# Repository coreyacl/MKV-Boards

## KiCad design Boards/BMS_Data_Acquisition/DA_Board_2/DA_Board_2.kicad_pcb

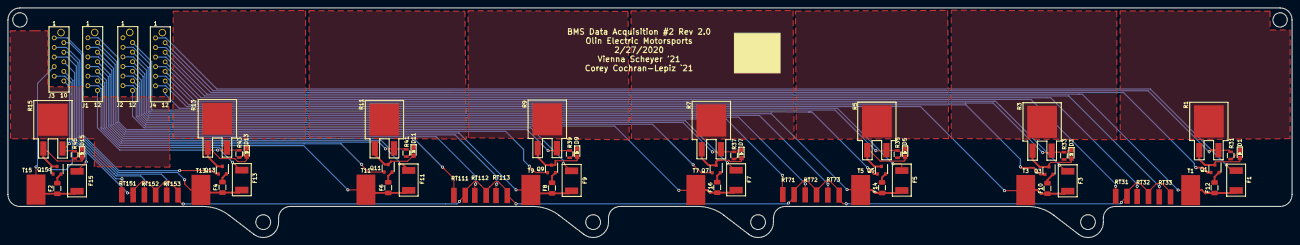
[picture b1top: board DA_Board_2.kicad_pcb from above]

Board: 2 copper layers, 340.1 x 60.8 mm, 72 parts (0 on the bottom side), 69 nets.

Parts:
D1, D3, D5, D7, D9, D11, D13, D15: LED_0805; LED_0805_OEM
F1, F3, F5, F7, F9, F11, F13, F15: 200mA_Fuse; Fuse_1812
F2, F4, F6, F8, F10, F12, F14, F16: 1.5A_Fuse; Fuse_1206
J1, J2, J4: MM_M_VT_12; micromatch_female_vert_12
J3: MM_M_VT_10; micromatch_female_vert_10
Q1, Q3, Q5, Q7, Q9, Q11, Q13, Q15: BSS308PE; SOT-23-3_OEM
R1, R3, R5, R7, R9, R11, R13, R15: R_3.3_25W_TO163; PWR163
R31, R33, R35, R37, R39, R41, R43, R45: R_475; R_0805_OEM
RT31, RT32, RT33, RT71, RT72, RT73, RT111, RT112, RT113, RT151, RT152, RT153: Thermistor
T1, T3, T5, T7, T9, T11, T13, T15: Tab_Connect_BMS; Tab_connect_BMS

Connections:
/C1: F1.2, J4.1
/C3: F3.2, J4.8
/C3_T1: J4.7, RT31.1
/C3_T2: J4.6, RT32.1
/C3_T3: J4.5, RT33.1
/C5: F5.2, J4.12
/C7: F7.2, J2.8
/C7_T1: J2.7, RT71.1
/C7_T2: J2.6, RT72.1
/C7_T3: J2.5, RT73.1
/C9: F9.2, J2.12
/C11: F11.2, J1.7
/C11_T1: J1.6, RT111.1
/C11_T2: J1.5, RT112.1
/C11_T3: J1.4, RT113.1
/C13: F13.2, J1.11
/C15: F15.2, J3.8
/C15_T1: J3.5, RT151.1
/C15_T2: J3.4, RT152.1
/C15_T3: J3.3, RT153.1
/GND1: J3.6, RT31.2, RT32.2, RT33.2, RT71.2, RT72.2, RT73.2, RT111.2, RT112.2, RT113.2, RT151.2, RT152.2, RT153.2
/PWR1: J4.2, R1.2, R31.2
/PWR2: F1.1, F12.1, J4.4, T1.1
/PWR3: J4.9, R3.2, R33.2
/PWR4: F3.1, F10.1, J4.11, T3.1
/PWR5: J2.2, R5.2, R35.2
/PWR6: F5.1, F14.1, J2.4, T5.1
/PWR7: J2.9, R7.2, R37.2
/PWR8: F7.1, F16.1, J2.11, T7.1
/PWR9: J1.1, R9.2, R39.2
/PWR10: F8.1, F9.1, J1.3, T9.1
/PWR11: J1.8, R11.2, R41.2
/PWR12: F6.1, F11.1, J1.10, T11.1
/PWR13: J1.12, R13.2, R43.2
/PWR14: F4.1, F13.1, J3.2, T13.1
/PWR15: J3.10, R15.2, R45.2
/PWR16: F2.1, F15.1, J3.7, T15.1
/Q1: J4.3, Q1.1
/Q3: J4.10, Q3.1
/Q5: J2.3, Q5.1
/Q7: J2.10, Q7.1
/Q9: J1.2, Q9.1
/Q11: J1.9, Q11.1
/Q13: J3.1, Q13.1
/Q15: J3.9, Q15.1
unnamed: D1.1, R31.1
unnamed: D1.2, Q1.3, R1.1
unnamed: D3.1, R33.1
unnamed: D3.2, Q3.3, R3.1
unnamed: D5.1, R35.1
unnamed: D5.2, Q5.3, R5.1
unnamed: D7.1, R37.1
unnamed: D7.2, Q7.3, R7.1
unnamed: D9.1, R39.1
unnamed: D9.2, Q9.3, R9.1
unnamed: D11.1, R41.1
unnamed: D11.2, Q11.3, R11.1
unnamed: D13.1, R43.1
unnamed: D13.2, Q13.3, R13.1
unnamed: D15.1, R45.1
unnamed: D15.2, Q15.3, R15.1
unnamed: F2.2, Q15.2
unnamed: F4.2, Q13.2
unnamed: F6.2, Q11.2
unnamed: F8.2, Q9.2
unnamed: F10.2, Q3.2
unnamed: F12.2, Q1.2
unnamed: F14.2, Q5.2
unnamed: F16.2, Q7.2

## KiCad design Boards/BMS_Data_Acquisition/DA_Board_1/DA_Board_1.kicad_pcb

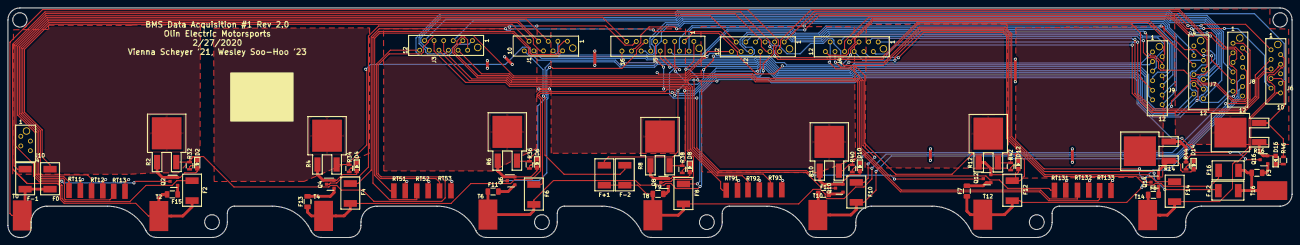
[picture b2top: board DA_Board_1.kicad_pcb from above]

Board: 2 copper layers, 340.1 x 60.8 mm, 85 parts (1 on the bottom side), 103 nets.

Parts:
D2, D4, D6, D8, D10, D12, D14, D16: LED_0805; LED_0805_OEM
F0, F2, F4, F6, F8, F10, F12, F14, F16: 200mA_Fuse; Fuse_1812
F1, F3, F5, F7, F9, F11, F13, F15: 1.5A_Fuse; Fuse_1206
F+1, F+2: 200mA_Fuse; Fuse_1812
F-1, F-2: 200mA_Fuse; Fuse_1812
J1, J6: MM_M_VT_10; micromatch_female_vert_10
J2, J3, J4, J7, J8#2, J9: MM_M_VT_12; micromatch_female_vert_12
J5: MM_M_VT_16; micromatch_female_vert_16
J8, J10: MM_F_VT_04; micromatch_female_vert_4
Q2, Q4, Q6, Q8, Q10, Q12, Q14, Q16: BSS308PE; SOT-23-3_OEM
R2, R4, R6, R8, R10, R12, R14, R16: R_3.3_25W_TO163; PWR163
R32, R34, R36, R38, R40, R42, R44, R46: R_475; R_0805_OEM
RT11, RT12, RT13, RT51, RT52, RT53, RT91, RT92, RT93, RT131, RT132, RT133: Thermistor
T0, T2, T4, T6, T8, T10, T12, T14, T16: Tab_Connect_BMS; Tab_connect_BMS

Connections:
/C0: F0.2, J1.9
/C1: J1.8, J9.1
/C1_T1: J1.7, RT11.1
/C1_T2: J1.6, RT12.1
/C1_T3: J1.5, RT13.1
/C2: F2.2, J2.11
/C3: J1.4, J9.8
/C3_T1: J2.9, J9.7
/C3_T2: J2.8, J9.6
/C3_T3: J2.7, J9.5
/C4: F4.2, J2.10
/C5: J1.3, J9.12
/C5_T1: J1.2, RT51.1
/C5_T2: J1.1, RT52.1
/C5_T3: J3.12, RT53.1
/C6: F6.2, J2.6
/C7: J3.11, J7.8
/C7_T1: J2.2, J7.7
/C7_T2: J2.1, J7.6
/C7_T3: J4.12, J7.5
/C8: F8.2, J2.3
/C9: J3.10, J7.12
/C9_T1: J3.9, RT91.1
/C9_T2: J3.8, RT92.1
/C9_T3: J3.7, RT93.1
/C10: F10.2, J4.11
/C11: J3.6, J8#2.7
/C11_T1: J4.9, J8#2.6
/C11_T2: J4.8, J8#2.5
/C11_T3: J4.7, J8#2.4
/C12: F12.2, J4.10
/C13: J3.5, J8#2.11
/C13_T1: J3.4, RT131.1
/C13_T2: J3.3, RT132.1
/C13_T3: J3.2, RT133.1
/C14: F14.2, J4.6
/C15: J3.1, J6.8
/C15_T1: J4.3, J6.5
/C15_T2: J4.2, J6.4
/C15_T3: J4.1, J6.3
/C16: F16.2, J4.4
/GND1: J2.12, J6.6, RT11.2, RT12.2, RT13.2, RT51.2, RT52.2, RT53.2, RT91.2, RT92.2, RT93.2, RT131.2, RT132.2, RT133.2
/PWR1: F0.1, F-1.1, J9.2, T0.1
/PWR2: J9.4, R2.2, R32.2
/PWR3: F2.1, F15.1, J9.9, T2.1
/PWR4: J9.11, R4.2, R34.2
/PWR5: F4.1, F13.1, J7.2, T4.1
/PWR6: J7.4, R6.2, R36.2
/PWR7: F6.1, F11.1, J7.9, T6.1
/PWR8: J7.11, R8.2, R38.2
/PWR9: F8.1, F9.1, F+1.1, F-2.1, J8#2.1, T8.1
/PWR10: J8#2.3, R10.2, R40.2
/PWR11: F1.1, F10.1, J8#2.8, T10.1
/PWR12: J8#2.10, R12.2, R42.2
/PWR13: F7.1, F12.1, J8#2.12, T12.1
/PWR14: J6.2, R14.2, R44.2
/PWR15: F5.1, F14.1, J6.10, T14.1
/PWR16: J6.7, R16.2, R46.2
/Q1: J5.16, J9.3
/Q2: J5.15, Q2.1
/Q3: J5.14, J9.10
/Q4: J5.13, Q4.1
/Q5: J5.12, J7.3
/Q6: J5.11, Q6.1
/Q7: J5.10, J7.10
/Q8: J5.9, Q8.1
/Q9: J5.8, J8#2.2
/Q10: J5.7, Q10.1
/Q11: J5.6, J8#2.9
/Q12: J5.5, Q12.1
/Q13: J5.4, J6.1
/Q14: J5.3, Q14.1
/Q15: J5.2, J6.9
/Q16: J5.1, Q16.1
/V+1: F+1.2, J4.5
/V+2: F+2.2, J2.5
/V-1: F-1.2, J2.4
/V-2: F-2.2, J1.10
unnamed: D2.1, R32.1
unnamed: D2.2, Q2.3, R2.1
unnamed: D4.1, R34.1
unnamed: D4.2, Q4.3, R4.1
unnamed: D6.1, R36.1
unnamed: D6.2, Q6.3, R6.1
unnamed: D8.1, R38.1
unnamed: D8.2, Q8.3, R8.1
unnamed: D10.1, R40.1
unnamed: D10.2, Q10.3, R10.1
unnamed: D12.1, R42.1
unnamed: D12.2, Q12.3, R12.1
unnamed: D14.1, R44.1
unnamed: D14.2, Q14.3, R14.1
unnamed: D16.1, R46.1
unnamed: D16.2, Q16.3, R16.1
unnamed: F1.2, Q10.2
unnamed: F3.2, Q16.2
unnamed: F5.2, Q14.2
unnamed: F7.2, Q12.2
unnamed: F9.2, Q8.2
unnamed: F11.2, Q6.2
unnamed: F13.2, Q4.2
unnamed: F15.2, Q2.2
unnamed: F3.1, F16.1, F+2.1, T16.1

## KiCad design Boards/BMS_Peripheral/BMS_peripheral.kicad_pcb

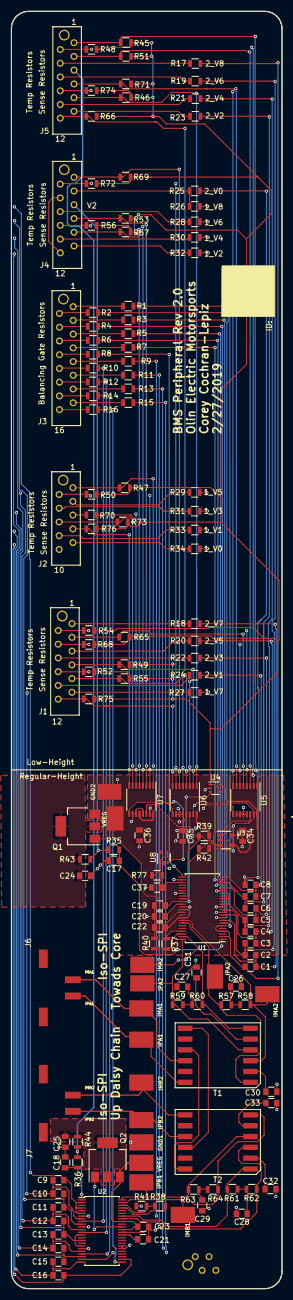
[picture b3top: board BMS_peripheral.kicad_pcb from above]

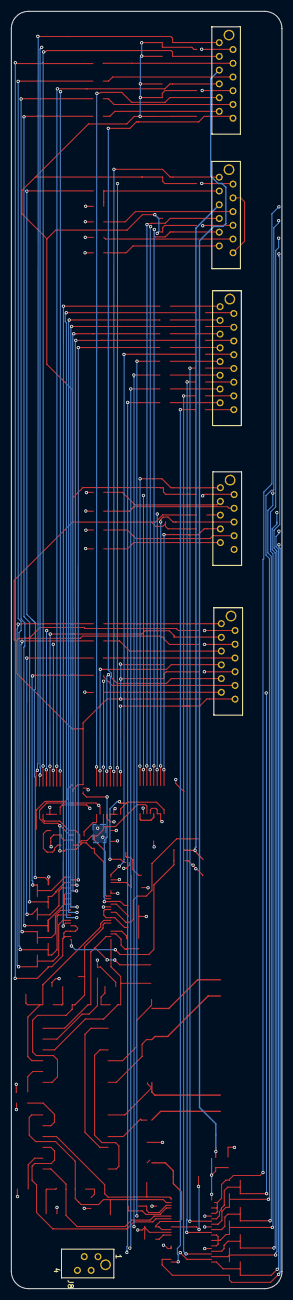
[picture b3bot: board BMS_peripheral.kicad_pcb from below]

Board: 4 copper layers, 50.0 x 236.2 mm, 148 parts (6 on the bottom side), 138 nets.

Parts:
C1, C2, C3, C4, C5, C6, C7, C8, C9, C10, C11, C12, C13, C14, C15, C16, C26, C27, C28, C29, C30, C31, C32, C33, C37: C_10nF; C_0805_OEM
C17, C18, C24, C25: C_0.1uF; C_0805_OEM
C19, C20, C21, C22, C23: 1uF; C_0805_OEM
C34, C35, C36: C_1uF; C_0805_OEM
J1, J4: MM_F_VT_12; micromatch_female_vt_12
J2: MM_F_VT_10; micromatch_female_vert_10
J3: MM_F_VT_16; micromatch_female_vert_16
J5: MM_M_VT_12; micromatch_female_vt_12
J6, J7: MicroFit_RA_V_2_SMD; MicroFit_RA_2_SMD
J8: MM_F_VT_04; micromatch_female_vert_4
Q1, Q2: NSS1C201MZ4; SOT-223
R1, R2, R3, R4, R5, R6, R7, R8, R9, R10, R11, R12, R13, R14, R15, R16, R39, R42: R_4.99K; R_0805_OEM
R17, R18, R19, R20, R21, R22, R23, R24, R25, R26, R27, R28, R29, R30, R31, R32, R33, R34, R35, R36, R43, R44, R77: R_100; R_0805_OEM
R37, R38, R40, R41: R_1K; R_0805_OEM
R45, R46, R47, R48, R49, R50, R51, R52, R53, R54, R55, R56, R65, R66, R67, R68, R69, R70, R71, R72, R73, R74, R75, R76: R_100K; R_0805_OEM
R57, R58, R59, R60, R61, R62, R63, R64: R_60.4; R_0805_OEM
T1, T2: T_LAN_SM91501ALE
TP1, TP2, TP3, TP4, TP5, TP6, TP7, TP8, TP9, TP10, TP11, TP12, TP13, TP14: Test_Point_SMD
U1, U2: LTC6811-1; TSSOP-48_LTC6811-1
U3: 24AA01; SOT-23-5_OEM_24AA01
U4, U8: MCP6001T-I-LT; SOT-353_SC-70-5
U5, U6, U7: LTC1380IGN; SSOP-16_3.9x4.9mm_P0.635mm

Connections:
/C0: J2.9, R34.1
/C1: J2.8, R33.1
/C1_T1: J2.7, R76.2, U7.8
/C1_T2: J2.6, R73.2, U7.7
/C1_T3: J2.5, R70.2, U7.6
/C2: J4.11, R32.1
/C3: J2.4, R31.1
/C3_T1: J4.9, R67.2, U7.5
/C3_T2: J4.8, R56.2, U7.4
/C3_T3: J4.7, R53.2, U7.3
/C4: J4.10, R30.1
/C5: J2.3, R29.1
/C5_T1: J2.2, R50.2, U7.2
/C5_T2: J2.1, R47.2, U7.1
/C5_T3: J1.12, R75.2, U6.8
/C6: J4.6, R28.1
/C7: J1.11, R27.1
/C7_T1: J4.2, R72.2, U6.7
/C7_T2: J4.1, R69.2, U6.6
/C7_T3: J5.12, R66.2, U6.5
/C8: J4.3, R25.1, R26.1
/C9: J1.10, R24.1
/C9_T1: J1.9, R55.2, U6.4
/C9_T2: J1.8, R52.2, U6.3
/C9_T3: J1.7, R49.2, U6.2
/C10: J5.11, R23.1
/C11: J1.6, R22.1
/C11_T1: J5.9, R46.2, U6.1
/C11_T2: J5.8, R74.2, U5.8
/C11_T3: J5.7, R71.2, U5.7
/C12: J5.10, R21.1
/C13: J1.5, R20.1
/C13_T1: J1.4, R68.2, U5.6
/C13_T2: J1.3, R65.2, U5.5
/C13_T3: J1.2, R54.2, U5.4
/C14: J5.6, R19.1
/C15: J1.1, R18.1
/C15_T1: J5.3, R51.2, U5.3
/C15_T2: J5.2, R48.2, U5.2
/C15_T3: J5.1, R45.2, U5.1
/C16: J5.4, R17.1
/GND1: C18.2, C21.2, C23.2, C25.2, C28.2, C29.2, C32.2, C33.2, J4.4, J4.12, R41.2, TP1.1, U2.30, U2.31, U2.36
/GND2: C17.2, C19.2, C20.2, C22.2, C24.2, C26.2, C27.2, C30.2, C31.2, C34.2, C35.2, C36.2, C37.2, J2.10, R40.2, TP2.1, U1.30, U1.31, U1.36, U3.2, U3.5, U4.2, U5.10, U5.11, U5.12, U5.13, U6.10, U6.11, U6.12, U7.10, U7.11, U7.13, U8.2
/IMA1: R62.2, T2.3, U2.41
/IMA2: R58.2, T1.3, TP5.1, U1.41
/IMB1: R64.2, T2.6, TP7.1, U2.47
/IMB2: R60.2, T1.6, TP10.1, U1.47
/IPA1: R61.1, T2.1, U2.42
/IPA2: R57.1, T1.1, TP8.1, U1.42
/IPB1: R63.1, T2.4, TP6.1, U2.48
/IPB2: R59.1, T1.4, TP9.1, U1.48
/Q1: J3.16, R16.2
/Q2: J3.15, R15.2
/Q3: J3.14, R14.2
/Q4: J3.13, R13.2
/Q5: J3.12, R12.2
/Q6: J3.11, R11.2
/Q7: J3.10, R10.2
/Q8: J3.9, R9.2
/Q9: J3.8, R8.2
/Q10: J3.7, R7.2
/Q11: J3.6, R6.2
/Q12: J3.5, R5.2
/Q13: J3.4, R4.2
/Q14: J3.3, R3.2
/Q15: J3.2, R2.2
/Q16: J3.1, R1.2
/SCL: R42.2, U1.33, U3.1, U5.15, U6.15, U7.15
/SDA: R39.2, U1.32, U3.3, U5.14, U6.14, U7.14
/TEMP_SENSE: C37.1, R77.1, U1.27
/V+1: J5.5, R36.1, R44.1
/V+2: J4.5, R35.1, R43.1
/VREF2: R45.1, R46.1, R47.1, R48.1, R49.1, R50.1, R51.1, R52.1, R53.1, R54.1, R55.1, R56.1, R65.1, R66.1, R67.1, R68.1, R69.1, R70.1, R71.1, R72.1, R73.1, R74.1, R75.1, R76.1, U4.1, U4.4
/VREG: C22.1, C34.1, C35.1, C36.1, Q1.3, R39.1, R42.1, TP3.1, U1.37, U1.40, U3.4, U4.5, U5.16, U6.13, U6.16, U7.12, U7.16, U8.5
/~DIS~1: R16.1, U2.25
/~DIS~2: R15.1, U2.23
/~DIS~3: R14.1, U2.21
/~DIS~4: R13.1, U2.19
/~DIS~6: R12.1, U2.13
/~DIS~7: R11.1, U2.11
/~DIS~8: R10.1, U2.9
/~DIS~9: R9.1, U2.7
unnamed: C1.1, R17.2, U1.2, U1.4, U1.6
unnamed: C1.2, C2.1, R18.2, U1.8
unnamed: C2.2, C3.1, R19.2, U1.10
unnamed: C3.2, C4.1, R20.2, U1.12
unnamed: C4.2, C5.1, R21.2, U1.14, U1.16, U1.18
unnamed: C5.2, C6.1, R22.2, U1.20
unnamed: C6.2, C7.1, R23.2, U1.22
unnamed: C7.2, C8.1, R24.2, U1.24
unnamed: C8.2, R25.2, U1.26
unnamed: C9.1, R26.2, U2.2, U2.4, U2.6
unnamed: C9.2, C10.1, R27.2, U2.8
unnamed: C10.2, C11.1, R28.2, U2.10
unnamed: C11.2, C12.1, R29.2, U2.12
unnamed: C12.2, C13.1, R30.2, U2.14, U2.16, U2.18
unnamed: C13.2, C14.1, R31.2, U2.20
unnamed: C14.2, C15.1, R32.2, U2.22
unnamed: C15.2, C16.1, R33.2, U2.24
unnamed: C16.2, R34.2, U2.26
unnamed: C17.1, R35.2, U1.1
unnamed: C18.1, R36.2, U2.1
unnamed: C19.1, U1.34, U4.3
unnamed: C20.1, U1.35
unnamed: C21.1, U2.35
unnamed: C23.1, Q2.3, TP4.1, U2.37, U2.40
unnamed: C24.1, Q1.2, Q1.4, R43.2
unnamed: C25.1, Q2.2, Q2.4, R44.2
unnamed: C26.1, R57.2, R58.1
unnamed: C27.1, R59.2, R60.1
unnamed: C28.1, R61.2, R62.1
unnamed: C29.1, R63.2, R64.1
unnamed: C30.1, T1.2
unnamed: C31.1, T1.5
unnamed: C32.1, T2.2
unnamed: C33.1, T2.5
unnamed: J6.1, T1.12, TP13.1
unnamed: J6.2, T1.10, TP14.1
unnamed: J7.1, T2.9, TP11.1
unnamed: J7.2, T2.7, TP12.1
unnamed: Q1.1, U1.38
unnamed: Q2.1, U2.38
unnamed: R1.1, U1.7
unnamed: R2.1, U1.9
unnamed: R3.1, U1.11
unnamed: R4.1, U1.13
unnamed: R5.1, U1.19
unnamed: R6.1, U1.21
unnamed: R7.1, U1.23
unnamed: R8.1, U1.25
unnamed: R37.1, R40.1, U1.46
unnamed: R37.2, U1.45
unnamed: R38.1, R41.1, U2.46
unnamed: R38.2, U2.45
unnamed: R77.2, U8.1, U8.4
unnamed: T1.7, T2.10
unnamed: T1.9, T2.12
unnamed: U5.9, U6.9, U7.9, U8.3

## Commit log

2020-03-06 slight changes for BMS boards before shipping
